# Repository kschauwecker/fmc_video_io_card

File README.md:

# FMC Video IO Card
This FMC module features a MIPI Rx and a HDMI Tx interface. It was designed for use with the TEG2000 SOM in combination with the TE0701 carrier by Trenz Electronics, which features a GateMate FPGA by Cologne Chip.

Please see the [blog post on Elektronaut](https://elektronaut.tech/en/fpga/driving-full-hd-video-with-the-cologne-chip-gatemate-fpga/)
for more details on this project.

## Core Features
* The MIPI interface uses a resistor network to connect HS and LP signal to different pins
* For the HDMI interface a parallel RGB converter IC is used (so the FPGA will need to output parallel RGB)
* An additional HyperRAM is provided which can serve as a frame buffer

## Project Status
This is an ongoing project. Only the following hardware parts have been tested and are confirmed to work

* HDMI interface running at 720p @ 60Hz
* HDMI interface running at 1080p @ 60Hz

Test for the MIPI interface and HyperRAM are still pending.

## Known Issues
* The card is a little too large and overlaps slightly with the SOM when mounted on the TE0701 carrier. The standoff screws on the SOM must be removed

## FPGA Software
The FPGA-implementation for the parallel RGB interface is available here:

https://github.com/kschauwecker/gatemate_parallel_rgb

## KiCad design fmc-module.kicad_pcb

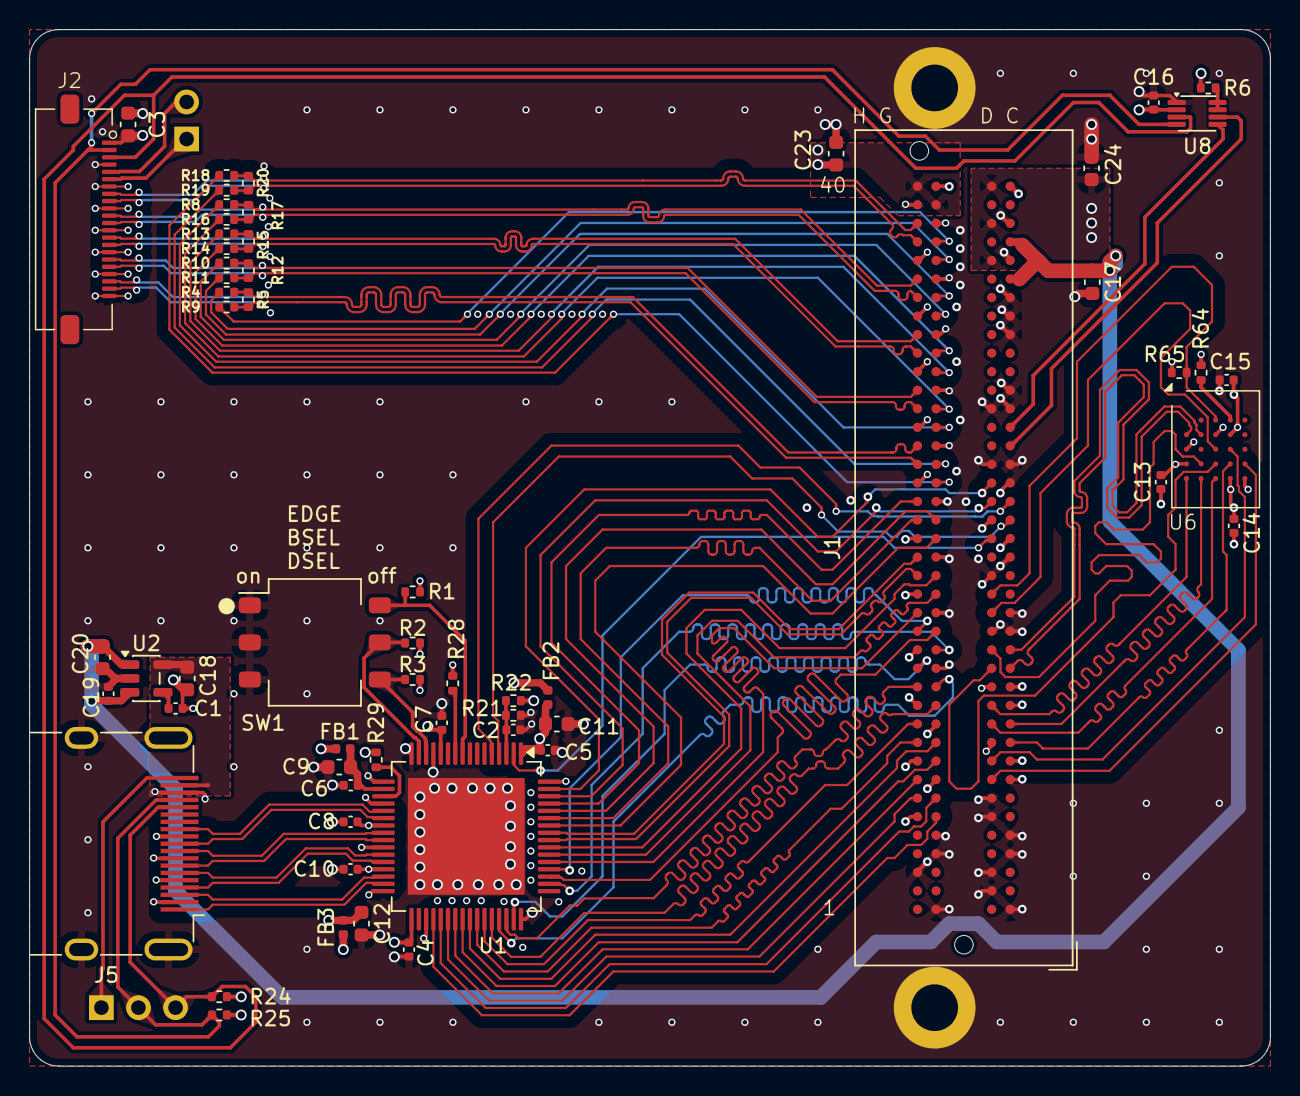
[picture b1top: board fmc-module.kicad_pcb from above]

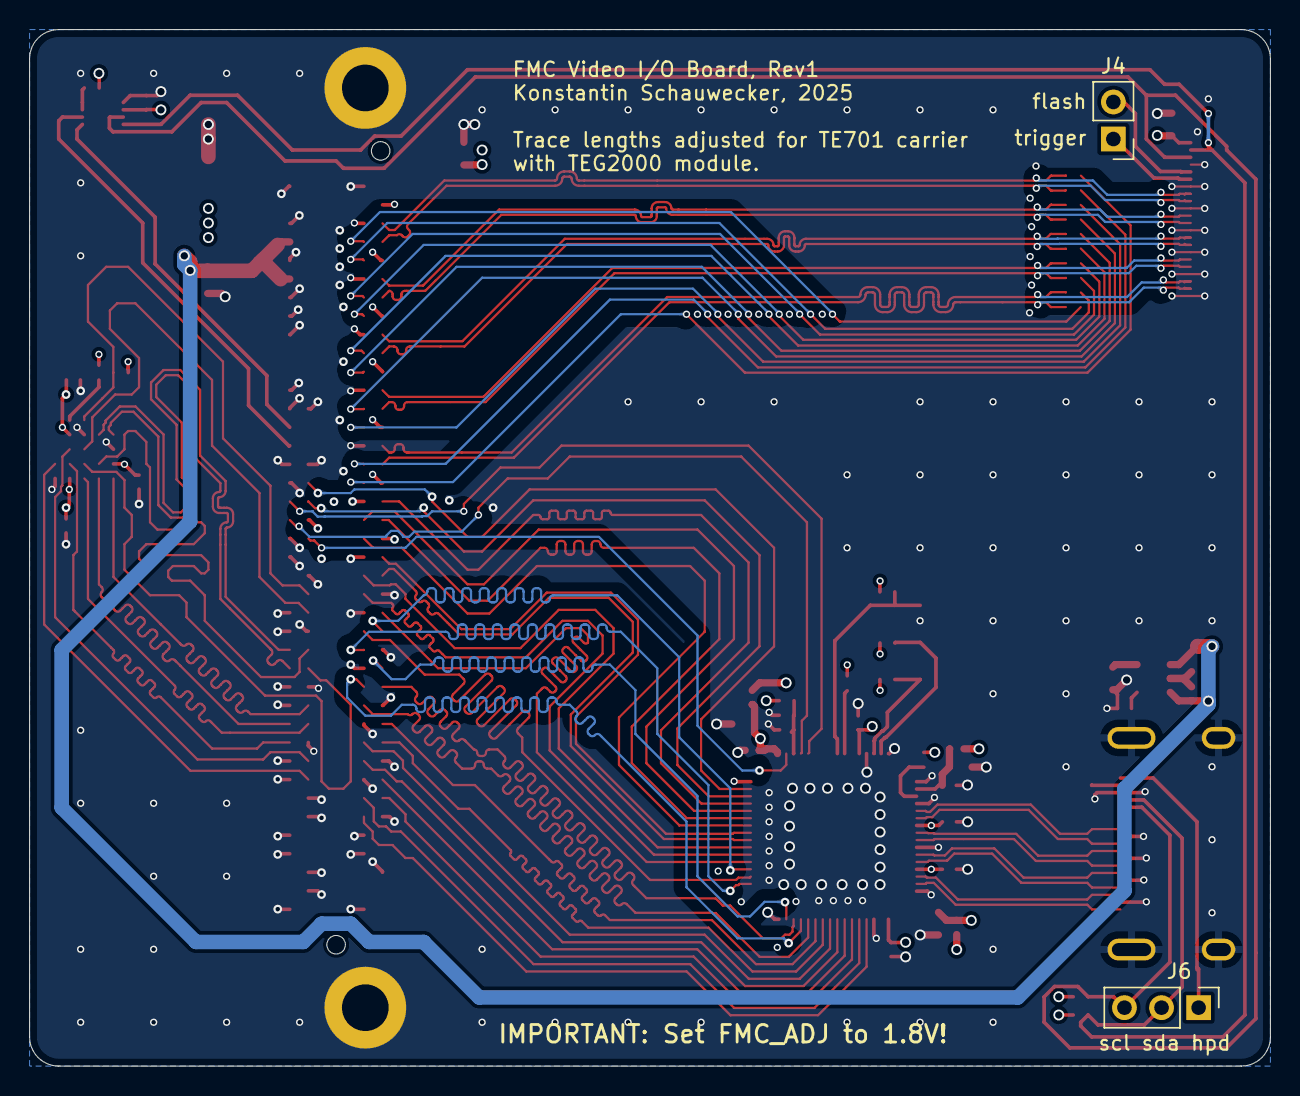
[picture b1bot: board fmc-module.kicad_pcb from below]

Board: 4 copper layers, 85.0 x 71.0 mm, 64 parts (2 on the bottom side), 93 nets.

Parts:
C1, C2, C4, C5, C6, C7, C8, C10, C13, C14, C15, C16, C19: 0.1uF; C_0402_1005Metric
C3, C9, C11, C12, C17, C18, C20, C23, C24: 10uF; C_0603_1608Metric
FB1, FB2, FB3: 600R @ 100 MHz; L_0402_1005Metric
H1, H2: MountingHole_Pad; MountingHole_3.2mm_M3_DIN965_Pad
J1: Samtec_FMC_ASP-134604-01_4x40_Vertical
J2: 501951-2230; connector-molex-505110-2291
J4: Conn_01x02; PinHeader_1x02_P2.54mm_Vertical
J5: HDMI_A; HDMI_A_Molex_208658-1001_Horizontal
J6: Conn_01x03; PinHeader_1x03_P2.54mm_Vertical
R1, R2, R3, R6, R21, R22, R24, R25, R28, R64, R65: 10k; R_0402_1005Metric
R4, R8, R9, R10, R11, R13, R14, R16, R18, R19: 100R / 1%; R_0402_1005Metric
R5, R12, R15, R17, R20: 150R / 1%; R_0402_1005Metric
R29: 510R / 1%; R_0402_1005Metric
SW1: SW_DIP_x03; SW_DIP_SPSTx03_Slide_Omron_A6S-310x_W8.9mm_P2.54mm
U1: TFP410PAPR; Texas_TQFP-64-1EP_10x10mm_P0.5mm_EP8x8mm_Mask5x5mm
U2: MIC5205-5.0YM5; SOT-23-5
U6: W956D8NBRA5I; hyperram-winbond-8bit
U8: PCA9306DCU; VSSOP-8_2.3x2mm_P0.5mm

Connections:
+1V8: C13.1, C14.1, C15.1, C16.1, C23.1, J1.G39, J1.H40, R22.1, R64.2, R65.2, U6.B4 (VCC), U6.D1 (VCCQ), U6.E4 (VCCQ), U8.2 (VREF1)
+3V3: C3.1, C24.1, FB1.1, FB2.1, FB3.1, J1.D36, J1.D38, J1.D40, J2.1, R1.1, R2.1, R3.1, R6.1, R24.2, R25.2, R28.2, R29.1
+5V: C18.1, J5.18 (+5V), U2.5 (OUT)
+12V: C17.1, C19.1, C20.1, J1.C35, J1.C37, U2.1 (IN), U2.3 (EN)
/fmc/fmc_LA22_N: J1.G25, R19.2
/fmc/fmc_LA22_P: J1.G24, R18.1
/fmc/fmc_LA25_N: J1.G28, R16.2
/fmc/fmc_LA25_P: J1.G27, R8.1
/fmc/fmc_LA27_N: J1.C27, U8.5 (SDA2)
/fmc/fmc_LA27_P: J1.C26, U8.6 (SCL2)
/fmc/fmc_LA29_N: J1.G31, R14.2
/fmc/fmc_LA29_P: J1.G30, R13.1
/fmc/fmc_LA31_N: J1.G34, R11.2
/fmc/fmc_LA31_P: J1.G33, R10.1
/fmc/fmc_LA33_N: J1.G37, R9.2
/fmc/fmc_LA33_P: J1.G36, R4.1
/hdmi/hdmi_hpd: J5.19 (HPD), J6.1
/hdmi/hdmi_scl: J2.3, J5.15 (SCL), J6.3, R24.1, U8.3 (SCL1)
/hdmi/hdmi_sda: J2.2, J5.16 (SDA), J6.2, R25.1, U8.4 (SDA1)
/hdmi/rgb_data0: J1.D24, U1.63 (DATA0)
/hdmi/rgb_data1: J1.D23, U1.62 (DATA1)
/hdmi/rgb_data2: J1.H23, U1.61 (DATA2)
/hdmi/rgb_data3: J1.G22, U1.60 (DATA3)
/hdmi/rgb_data4: J1.H22, U1.59 (DATA4)
/hdmi/rgb_data5: J1.G21, U1.58 (DATA5)
/hdmi/rgb_data6: J1.G19, U1.55 (DATA6)
/hdmi/rgb_data7: J1.G18, U1.54 (DATA7)
/hdmi/rgb_data8: J1.H17, U1.53 (DATA8)
/hdmi/rgb_data9: J1.H16, U1.52 (DATA9)
/hdmi/rgb_data10: J1.G16, U1.51 (DATA10)
/hdmi/rgb_data11: J1.G15, U1.50 (DATA11)
/hdmi/rgb_data12: J1.H14, U1.47 (DATA12)
/hdmi/rgb_data13: J1.H13, U1.46 (DATA13)
/hdmi/rgb_data14: J1.G13, U1.45 (DATA14)
/hdmi/rgb_data15: J1.G12, U1.44 (DATA15)
/hdmi/rgb_data16: J1.H11, U1.43 (DATA16)
/hdmi/rgb_data17: J1.H10, U1.42 (DATA17)
/hdmi/rgb_data18: J1.G10, U1.41 (DATA18)
/hdmi/rgb_data19: J1.G09, U1.40 (DATA19)
/hdmi/rgb_data20: J1.H08, U1.39 (DATA20)
/hdmi/rgb_data21: J1.H07, U1.38 (DATA21)
/hdmi/rgb_data22: J1.G07, U1.37 (DATA22)
/hdmi/rgb_data23: J1.G06, U1.36 (DATA23)
/hdmi/tmds_ck_N: J5.12 (CK-), U1.21 (TXC-)
/hdmi/tmds_ck_P: J5.10 (CK+), U1.22 (TXC+)
/hdmi/tmds_d0_N: J5.9 (D0-), U1.24 (TX0-)
/hdmi/tmds_d0_P: J5.7 (D0+), U1.25 (TX0+)
/hdmi/tmds_d1_N: J5.6 (D1-), U1.27 (TX1-)
/hdmi/tmds_d1_P: J5.4 (D1+), U1.28 (TX1+)
/hdmi/tmds_d2_N: J5.3 (D2-), U1.30 (TX2-)
/hdmi/tmds_d2_P: J5.1 (D2+), U1.31 (TX2+)
/mipi/flash_sensor: J2.5, J4.2
/mipi/trigger_sensor: J2.6, J4.1
/mipi_hs_clk_N: J1.H31, J2.15, R14.1, R15.1
/mipi_hs_clk_P: J1.H32, J2.14, R13.2, R15.2
/mipi_hs_dat0_N: J1.H37, J2.9, R19.1, R20.1
/mipi_hs_dat0_P: J1.H38, J2.8, R18.2, R20.2
/mipi_hs_dat1_N: J1.H34, J2.12, R16.1, R17.1
/mipi_hs_dat1_P: J1.H35, J2.11, R8.2, R17.2
/mipi_hs_dat2_N: J1.H28, J2.18, R11.1, R12.1
/mipi_hs_dat2_P: J1.H29, J2.17, R10.2, R12.2
/mipi_hs_dat3_N: J1.H25, J2.21, R5.1, R9.1
/mipi_hs_dat3_P: J1.H26, J2.20, R4.2, R5.2
/ram/ram_dq0: J1.D14, U6.D3 (DQ0)
/ram/ram_dq1: J1.D15, U6.D2 (DQ1)
/ram/ram_dq2: J1.D09, U6.C4 (DQ2)
/ram/ram_dq3: J1.C10, U6.D4 (DQ3)
/ram/ram_dq4: J1.D08, U6.D5 (DQ4)
/ram/ram_dq5: J1.D11, U6.E3 (DQ5)
/ram/ram_dq6: J1.C11, U6.E2 (DQ6)
/ram/ram_dq7: J1.D12, U6.E1 (DQ7)
/ram_clk_N: J1.C14, U6.B1 (~CK)
/ram_clk_P: J1.C15, U6.B2 (CK)
/ram_csn: J1.D18, R65.1, U6.A3 (~CS)
/ram_rwds: J1.D17, U6.C3 (RWDS)
/rgb_clk_N: J1.H19, U1.56 (IDCK-)
/rgb_clk_P: J1.H20, U1.57 (IDCK+)
/rgb_de: J1.D21, U1.2 (DE)
/rgb_hsync: J1.C22, U1.4 (HSYNC)
/rgb_vsync: J1.C23, U1.5 (VSYNC)
GND: C1.2, C2.2, C3.2, C4.2, C5.2, C6.2, C7.2, C8.2, C9.2, C10.2, C11.2, C12.2, C13.2, C14.2, C15.2, C16.2, C17.2, C18.2, C19.2, C20.2, C23.2, C24.2, H1.1, H2.1, J1.C01, J1.C04, J1.C05, J1.C08, J1.C09, J1.C12, J1.C13, J1.C16, J1.C17, J1.C20, J1.C21, J1.C24, J1.C25, J1.C28, J1.C29, J1.C32, J1.C33, J1.C34, J1.C36, J1.C38, J1.C40, J1.D02, J1.D03, J1.D06, J1.D07, J1.D10, J1.D13, J1.D16, J1.D19, J1.D22, J1.D25, J1.D28, J1.G01, J1.G04, J1.G05, J1.G08, J1.G11, J1.G14, J1.G17, J1.G20, J1.G23, J1.G26, J1.G29, J1.G32, J1.G35, J1.G38, J1.G40, J1.H03, J1.H06, J1.H09, J1.H12, J1.H15, J1.H18, J1.H21, J1.H24, J1.H27, J1.H30, J1.H33, J1.H36, J1.H39, J2.4, J2.7, J2.10, J2.13, J2.16, J2.19, J2.22, J5.2 (D2S), J5.5 (D1S), J5.8 (D0S), J5.11 (CKS), J5.17 (GND), J5.SH, R21.1, SW1.1, SW1.2, SW1.3, U1.13 (ISEL/~RST), U1.16 (DGND), U1.17 (PGND), U1.20 (TGND), U1.26 (TGND), U1.32 (TGND), U1.35 (DKEN), U1.48 (DGND), U1.64 (DGND), U1.65 (EP), U2.2 (GND), U6.B3 (VSS), U6.C1 (VSSQ), U6.E5 (VSSQ), U8.1 (GND)
unnamed: C8.1, C10.1, C12.1, FB3.2, U1.23 (TVDD), U1.29 (TVDD)
unnamed: C4.1, C5.1, C7.1, C11.1, FB2.2, U1.1 (DVDD), U1.12 (DVDD), U1.33 (DVDD)
unnamed: R2.2, SW1.5, U1.15 (BSEL/SCL)
unnamed: R3.2, SW1.4, U1.14 (DSEL/SDA)
unnamed: R1.2, SW1.6, U1.9 (EDGE/HTPLG)
unnamed: C6.1, C9.1, FB1.2, U1.18 (PVDD)
unnamed: R29.2, U1.19 (TFADJ)
unnamed: C2.1, R21.2, R22.2, U1.3 (VREF)
unnamed: R28.1, U1.10 (~PD)
unnamed: C1.1, U2.4 (BP)
unnamed: R64.1, U6.A4 (~RESET)
unnamed: R6.2, U8.7 (VREF2), U8.8 (EN)

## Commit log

2025-12-01 Initial commit of electronics
2025-12-12 Added PCB photo
2026-01-03 Fixed wrong FMC pin labels
